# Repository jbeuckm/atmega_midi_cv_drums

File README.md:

atmega_midi_cv_drums
========================

This is designed to drive drum voice circuits similar to those found in the TR-808.

A CMOS addressable latch (CD4099) generates eight trigger signals. Uses TLV5628 octal DAC to generate eight “accent” trigger signals. All signals are approximately 1ms in duration. Triggers are to the positive rail and accents are scaled by velocity of the MIDI note. Accent signals in the 808 are intended to run 4-14V, so a +/-15V supply would be appropriate here.

Euro power connectors distribute the trigger and accent signals for eight drum voices, using the “gate” and “CV” buss conventions from eurorack. The power distribution daughterboard includes four dual rail-to-rail opamps that scale the DAC output accent signals up to the intended 4-14V range (given +/-15V supply). Each power connector provides power, trigger and accent signals to the connected module.

Assign each voice to a MIDI note number with this sysex message:

```0x77 0x08 0x01 <voice> <MIDI_note> 0xf7```

The voice number depends on which voice is connected to which dac output via the eurorack power style distribution connectors.

Power distribution daughterboard:

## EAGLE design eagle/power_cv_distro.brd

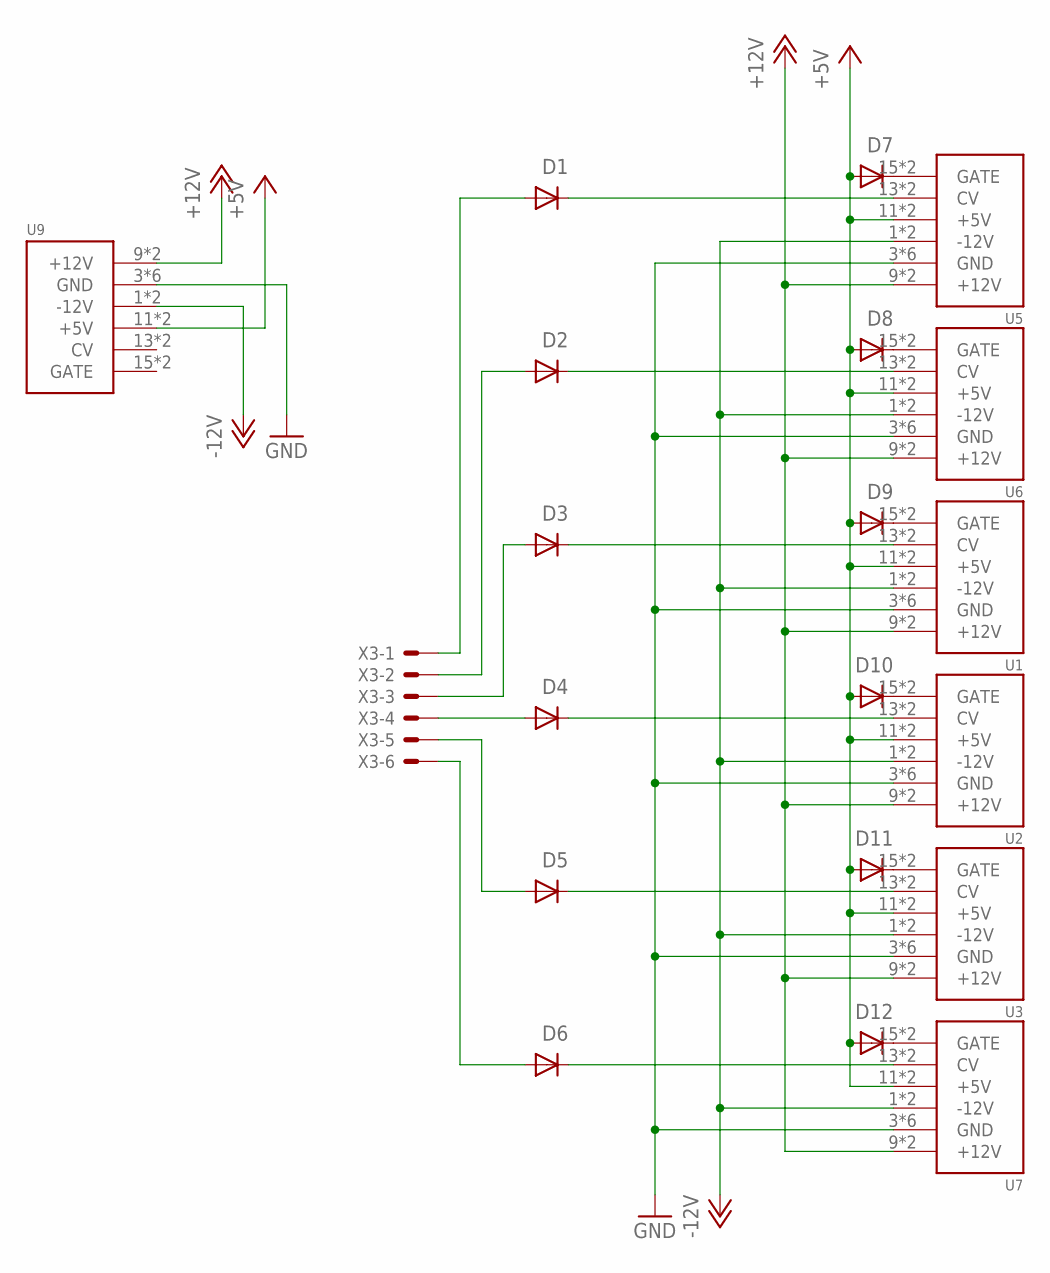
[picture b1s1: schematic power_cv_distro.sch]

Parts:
D1, D2, D3, D4, D5, D6, D7, D8, D9, D10, D11, D12: 1N4148DO35-7; DO35-7
U1, U2, U3, U5, U6, U7, U9: POWER; POWER_16
X3: 22-23-2061

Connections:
+5V: D7.A, D8.A, D9.A, D10.A, D11.A, D12.A, U1.11 (+5V), U1.12 (+5V), U2.11 (+5V), U2.12 (+5V), U3.11 (+5V), U3.12 (+5V), U5.11 (+5V), U5.12 (+5V), U6.11 (+5V), U6.12 (+5V), U7.11 (+5V), U7.12 (+5V), U9.11 (+5V), U9.12 (+5V)
+12V: U1.9 (+12V), U1.10 (+12V), U2.9 (+12V), U2.10 (+12V), U3.9 (+12V), U3.10 (+12V), U5.9 (+12V), U5.10 (+12V), U6.9 (+12V), U6.10 (+12V), U7.9 (+12V), U7.10 (+12V), U9.9 (+12V), U9.10 (+12V)
-12V: U1.1 (-12V), U1.2 (-12V), U2.1 (-12V), U2.2 (-12V), U3.1 (-12V), U3.2 (-12V), U5.1 (-12V), U5.2 (-12V), U6.1 (-12V), U6.2 (-12V), U7.1 (-12V), U7.2 (-12V), U9.1 (-12V), U9.2 (-12V)
GND: U1.3 (GND), U1.4 (GND), U1.5 (GND), U1.6 (GND), U1.7 (GND), U1.8 (GND), U2.3 (GND), U2.4 (GND), U2.5 (GND), U2.6 (GND), U2.7 (GND), U2.8 (GND), U3.3 (GND), U3.4 (GND), U3.5 (GND), U3.6 (GND), U3.7 (GND), U3.8 (GND), U5.3 (GND), U5.4 (GND), U5.5 (GND), U5.6 (GND), U5.7 (GND), U5.8 (GND), U6.3 (GND), U6.4 (GND), U6.5 (GND), U6.6 (GND), U6.7 (GND), U6.8 (GND), U7.3 (GND), U7.4 (GND), U7.5 (GND), U7.6 (GND), U7.7 (GND), U7.8 (GND), U9.3 (GND), U9.4 (GND), U9.5 (GND), U9.6 (GND), U9.7 (GND), U9.8 (GND)
unnamed: D1.A, X3.1
unnamed: D2.A, X3.2
unnamed: D3.A, X3.3
unnamed: D4.A, X3.4
unnamed: D5.A, X3.5
unnamed: D6.A, X3.6
unnamed: D1.C, U5.13 (CV), U5.14 (CV)
unnamed: D2.C, U6.13 (CV), U6.14 (CV)
unnamed: D3.C, U1.13 (CV), U1.14 (CV)
unnamed: D4.C, U2.13 (CV), U2.14 (CV)
unnamed: D5.C, U3.13 (CV), U3.14 (CV)
unnamed: D6.C, U7.13 (CV), U7.14 (CV)
unnamed: D7.C, U5.15 (GATE), U5.16 (GATE)
unnamed: D8.C, U6.15 (GATE), U6.16 (GATE)
unnamed: D9.C, U1.15 (GATE), U1.16 (GATE)
unnamed: D10.C, U2.15 (GATE), U2.16 (GATE)
unnamed: D11.C, U3.15 (GATE), U3.16 (GATE)
unnamed: D12.C, U7.15 (GATE), U7.16 (GATE)

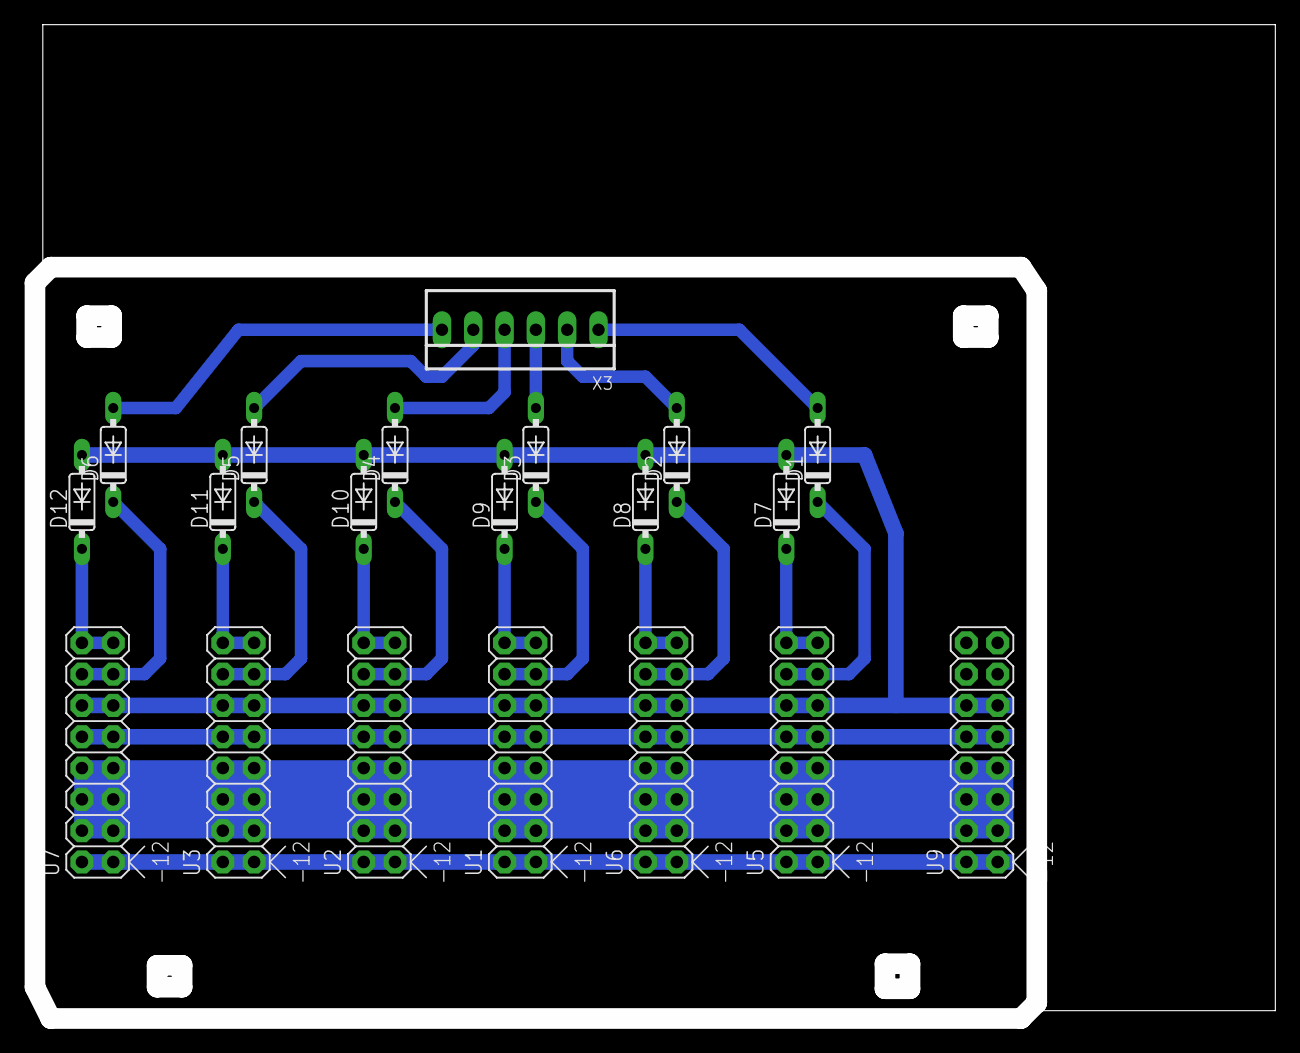
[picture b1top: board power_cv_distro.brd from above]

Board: 2 copper layers, 100.6 x 80.6 mm, 20 parts (0 on the bottom side), 22 nets.

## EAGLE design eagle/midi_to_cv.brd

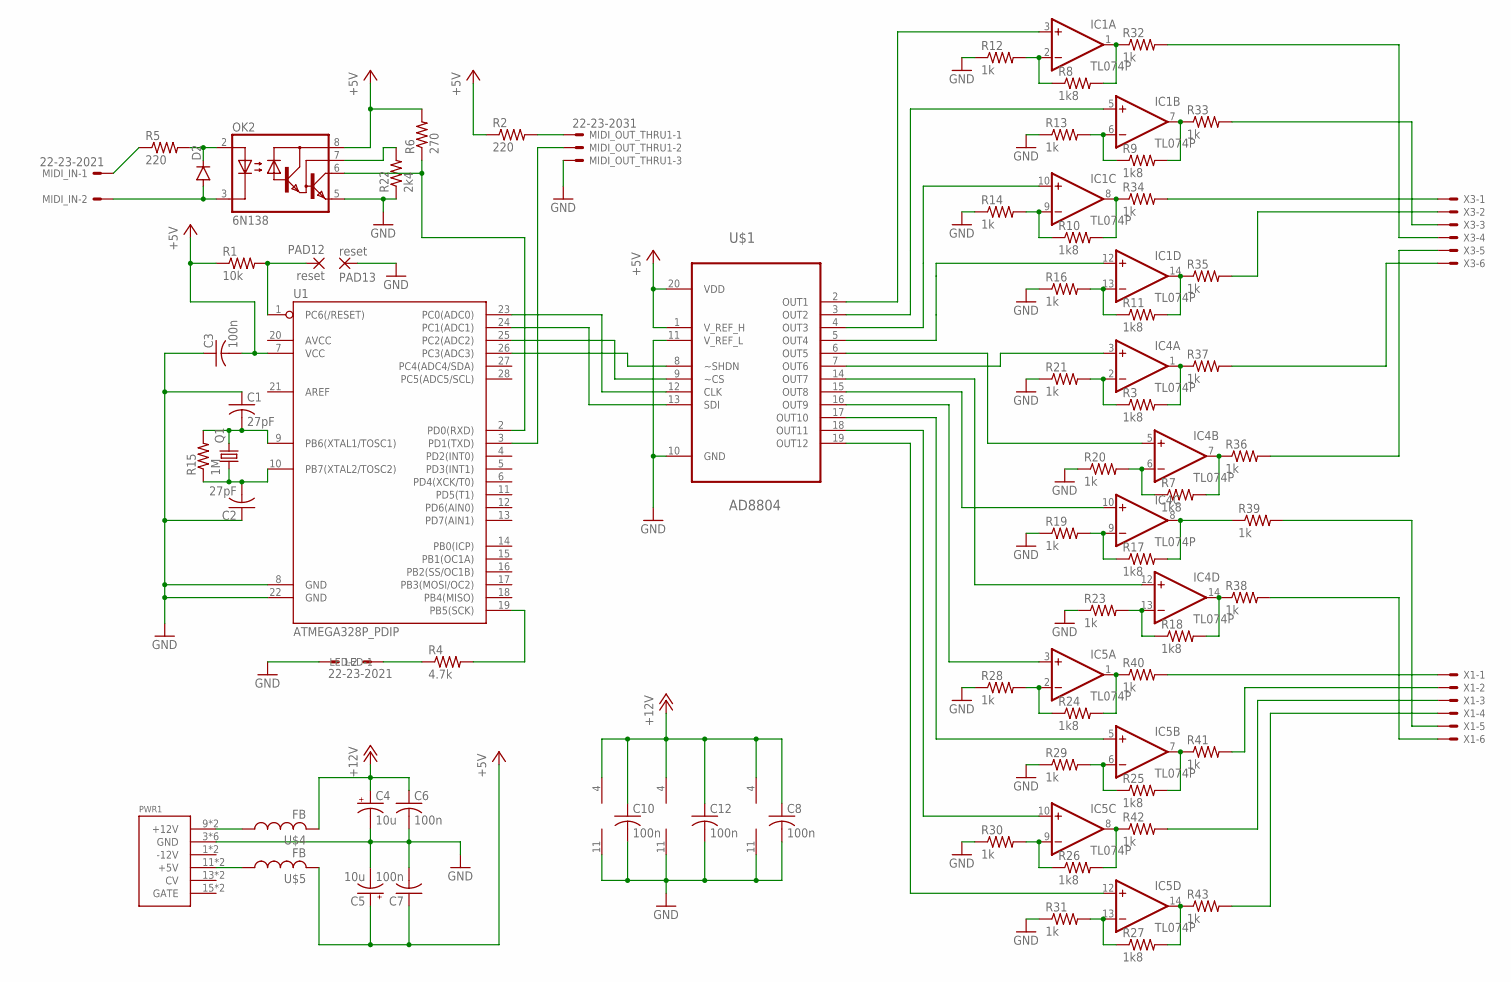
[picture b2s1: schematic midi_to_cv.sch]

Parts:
C1, C2: 27pF; C025-040X050
C3: 100n; C025-040X050
C4, C5: 10u; B45181A
C6, C7: 100n; C050-024X044
C8, C10, C12: 100n; C025-024X044
D2: DIODE1N4148; DIODE-1N4148
IC1, IC4, IC5: TL074P; DIL14
LED: 22-23-2021
MIDI_IN: 22-23-2021
MIDI_OUT_THRU1: 22-23-2031
OK2: 6N138; DIL08
PAD12, PAD13: reset; 2,54/0,9
PWR1: POWER; POWER_16
Q1: CRYSTALHC49U-V; HC49U-V
R1: 10k; 0207/10
R2: 220; 0207/10
R3, R7, R8, R9, R10, R11, R17, R18, R24, R25, R26, R27: 1k8; 0204V
R4: 4.7k; 0207/10
R5: 220; 0204/7
R6: 270; 0207/10
R12, R13, R14, R16, R19, R20, R21, R23, R28, R29, R30, R31, R33, R34, R35, R41, R42: 1k; 0204/5
R15: 1M; 0207/10
R22: 2k4; 0207/10
R32, R36, R37, R38, R39, R40, R43: 1k; 0204/7
U1: ATMEGA328P_PDIP; DIL28-3
U$1: AD8804; DIL20
U$4, U$5: FB
X1, X3: 22-23-2061

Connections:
+5V: C3.2, C5.+, C7.1, OK2.8 (VCC), R1.1, R2.1, R6.2, U1.7 (VCC), U$1.1 (V_REF_H), U$1.20 (VDD), U$5.P$2 (2)
+12V: C4.+, C6.1, C8.1, C10.1, C12.1, IC1.4 (V+), IC4.4 (V+), IC5.4 (V+), U$4.P$2 (2)
GND: C1.1, C2.1, C3.1, C4.-, C5.-, C6.2, C7.2, C8.2, C10.2, C12.2, IC1.11 (V-), IC4.11 (V-), IC5.11 (V-), LED.1, MIDI_OUT_THRU1.3, OK2.5 (GND), PAD13.1, PWR1.3 (GND), PWR1.4 (GND), PWR1.5 (GND), PWR1.6 (GND), PWR1.7 (GND), PWR1.8 (GND), R12.1, R13.1, R14.1, R16.1, R19.1, R20.1, R21.1, R22.1, R23.1, R28.1, R29.1, R30.1, R31.1, U1.8 (GND), U1.22 (GND), U$1.10 (GND), U$1.11 (V_REF_L)
unnamed: PAD12.1, R1.2, U1.1 (PC6(/RESET))
unnamed: PWR1.9 (+12V), PWR1.10 (+12V), U$4.P$1 (1)
unnamed: U1.26 (PC3(ADC3)), U$1.8 (~SHDN)
unnamed: C1.2, Q1.2, R15.2, U1.9 (PB6(XTAL1/TOSC1))
unnamed: C2.2, Q1.1, R15.1, U1.10 (PB7(XTAL2/TOSC2))
unnamed: U1.25 (PC2(ADC2)), U$1.9 (~CS)
unnamed: U1.23 (PC0(ADC0)), U$1.12 (CLK)
unnamed: U1.24 (PC1(ADC1)), U$1.13 (SDI)
unnamed: MIDI_OUT_THRU1.1, R2.2
unnamed: R4.2, U1.19 (PB5(SCK))
unnamed: LED.2, R4.1
unnamed: MIDI_OUT_THRU1.2, U1.3 (PD1(TXD))
unnamed: IC1.2 (-IN), R8.1, R12.2
unnamed: IC1.9 (-IN), R10.1, R14.2
unnamed: IC1.6 (-IN), R9.1, R13.2
unnamed: IC4.7 (OUT), R7.2, R36.1
unnamed: D2.A, MIDI_IN.2, OK2.3 (C)
unnamed: D2.C, OK2.2 (A), R5.2
unnamed: MIDI_IN.1, R5.1
unnamed: OK2.6 (VO), R6.1, U1.2 (PD0(RXD))
unnamed: IC1.13 (-IN), R11.1, R16.2
unnamed: IC4.8 (OUT), R17.2, R39.1
unnamed: IC4.14 (OUT), R18.2, R38.1
unnamed: IC4.9 (-IN), R17.1, R19.2
unnamed: R34.2, X3.1
unnamed: IC1.3 (+IN), U$1.2 (OUT1)
unnamed: IC1.5 (+IN), U$1.3 (OUT2)
unnamed: IC1.10 (+IN), U$1.4 (OUT3)
unnamed: IC1.12 (+IN), U$1.5 (OUT4)
unnamed: IC4.6 (-IN), R7.1, R20.2
unnamed: IC4.2 (-IN), R3.1, R21.2
unnamed: IC4.5 (+IN), U$1.6 (OUT5)
unnamed: IC4.3 (+IN), U$1.7 (OUT6)
unnamed: IC4.12 (+IN), U$1.14 (OUT7)
unnamed: IC4.10 (+IN), U$1.15 (OUT8)
unnamed: IC4.13 (-IN), R18.1, R23.2
unnamed: IC4.1 (OUT), R3.2, R37.1
unnamed: R35.2, X3.2
unnamed: R33.2, X3.3
unnamed: R32.2, X3.4
unnamed: IC5.3 (+IN), U$1.16 (OUT9)
unnamed: IC5.5 (+IN), U$1.17 (OUT10)
unnamed: IC5.10 (+IN), U$1.18 (OUT11)
unnamed: IC5.12 (+IN), U$1.19 (OUT12)
unnamed: IC5.2 (-IN), R24.1, R28.2
unnamed: IC5.6 (-IN), R25.1, R29.2
unnamed: IC5.9 (-IN), R26.1, R30.2
unnamed: IC5.13 (-IN), R27.1, R31.2
unnamed: IC5.1 (OUT), R24.2, R40.1
unnamed: IC5.7 (OUT), R25.2, R41.1
unnamed: IC5.8 (OUT), R26.2, R42.1
unnamed: IC5.14 (OUT), R27.2, R43.1
unnamed: IC1.1 (OUT), R8.2, R32.1
unnamed: IC1.7 (OUT), R9.2, R33.1
unnamed: IC1.8 (OUT), R10.2, R34.1
unnamed: IC1.14 (OUT), R11.2, R35.1
unnamed: R36.2, X3.5
unnamed: R37.2, X3.6
unnamed: R40.2, X1.1
unnamed: OK2.7 (VB), R22.2
unnamed: R41.2, X1.2
unnamed: PWR1.11 (+5V), PWR1.12 (+5V), U$5.P$1 (1)
unnamed: R42.2, X1.3
unnamed: R43.2, X1.4
unnamed: R39.2, X1.5
unnamed: R38.2, X1.6

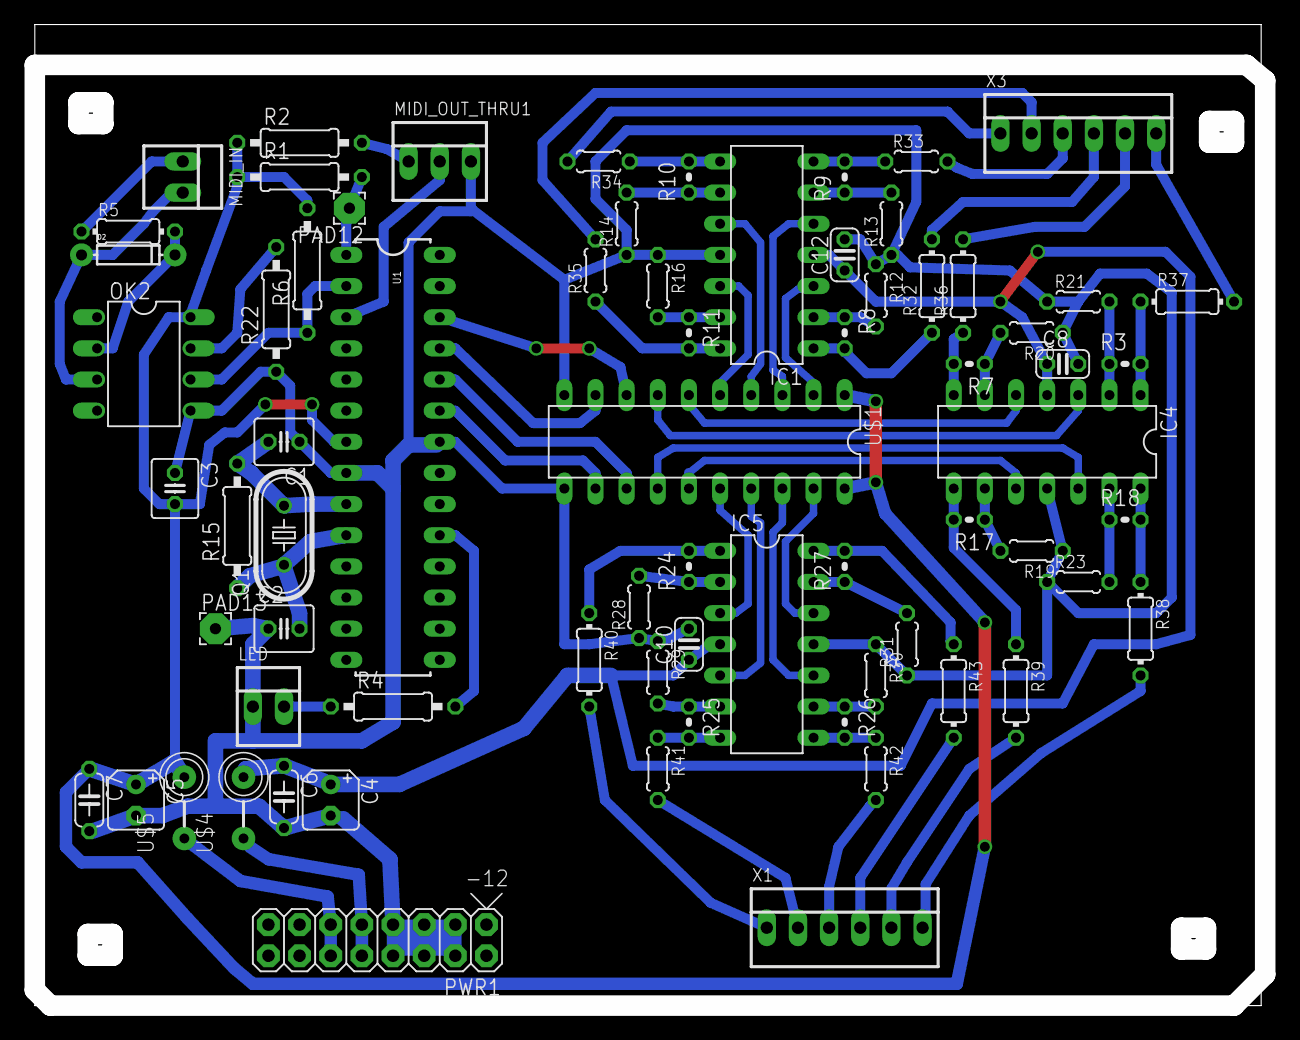
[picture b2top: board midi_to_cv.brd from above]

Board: 2 copper layers, 100.0 x 80.0 mm, 71 parts (0 on the bottom side), 69 nets.

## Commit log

2016-03-04 starting with files from polysynth
2016-03-05 level shift then latch cmos gate outs
2016-03-05 changing to use tlv5628
2016-03-05 midi uses header
2016-03-05 will start over with layout
2016-03-05 tidying up
2016-03-05 tlv5628
2016-03-05 tidier
2016-03-06 starting brd and dac library
2016-03-06 adding output resistors
2016-03-07 ribbon connectors with interleaved gate cna cv instead of power connectors
2016-03-08 connected midi to serial in
2016-03-08 ever closer to a route
2016-03-08 96 percent autorouting
2016-03-08 routed
2016-03-09 mid nineties autoroute
2016-03-09 a manual start
2016-03-09 cutout
2016-03-09 project file
2016-03-09 gcode
2016-03-09 new schemo image
2016-03-12 wrote pins from schematic
2016-03-12 latch code
2016-03-12 fixing up class and debugging
2016-03-12 cut and gates work
2016-03-13 dac working for note on velocity
2016-03-13 turning off 3ms trigger with ISR
2016-03-13 gate and dac on and off inside ISR working for eight notes simultaneous
2016-03-13 wider traces and starting distro board
2016-03-19 adding opamps
2016-03-19 feedbacks in place
2016-03-19 started routing
2016-03-19 opamps
2016-03-19 opamps in
2016-03-19 placement
2016-03-19 half routed
2016-03-19 output resistors
2016-03-19 route tweaked
2016-03-19 filtering power for scale opamps
2016-03-19 power distro gcode
2016-03-24 reverted to working midi board
2016-03-24 power distro brd into readme
2016-05-08 created the device for ad8804 12ch dac
2016-05-08 midi thru
2016-05-08 first opamps
2016-05-10 tweaks
2016-05-11 power dist do-over begins
2016-05-11 power dist to six only
2016-05-11 fixed molexes and tweaks
2016-05-11 fourth mounting hole
2016-05-18 untested code for ad8804 dac
2016-05-18 added layout png
2019-06-30 set note map from sysex

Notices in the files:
parts and their libraries:
SparkFun-DiscreteSemi: Licensing: Creative Commons ShareAlike 4.0 International - https://creativecommons.org/licenses/by-sa/4.0
